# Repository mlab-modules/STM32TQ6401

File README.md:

# STM32TQ6401 - Universal TQFP64 STM32 Microcontroller Module

The STM32TQ6401 is a universal microcontroller module designed for STM32 MCUs in TQFP64 packages. It offers a flexible platform for both development and deployment, with support for a wide range of STM32 devices and power configurations.

## Features

- Compatible with most STM32 MCUs in TQFP64 package (see note in schematics for exceptions)
- Direct battery operation from a CR2032 cell
- USB-C connector for both programming and external power input
- Standard MLAB pin headers for module interconnection to other MLAB modules
- Onboard 32.768 kHz and 16 MHz crystal oscillators for RTC and system clock
- Multiple LDO regulators providing 3.3V from USB or external 5V input
- USB power switch (TPS2051B) for host/device support
- Boot and reset buttons, debug header (SWD), and optional VCAP configuration

## Power Supply

- **Battery Operation:** Directly powered by a CR2032 cell; suitable for ultra-low power STM32 MCUs
- **USB Power:** Supplied through USB-C connector; LDO regulator converts 5V to 3.3V
- **External Power Input:** 2.6 V to 5.2 V via dedicated jumper or header

## Connectivity

- USB-C for firmware upload and serial communication
- SWD (Serial Wire Debug) header for in-circuit debugging
- MLAB standard headers for full I/O access

## Clock Sources

- **Y1:** 32.768 kHz crystal for RTC
- **Y2:** 16 MHz crystal for system clock

### Incompatible STM32 Devices
Some STM32 MCUs are not compatible with this module due to VCAP or other special pin requirements. These include (but are not limited to):

- STM32F030R4Tx, STM32F405RGTx, STM32H7xxRxTx
- STM32G4xxRxTx, STM32L5xxRxTxQ, STM32U5xxRxTxQ

Refer to schematic details for a complete list of incompatible devices.

### Pin Variants

Special attention is required for the following pins due to variant functions:

- VBAT / VLCD
- VCAP / VDDUSB
- BOOT0 / PH3

Refer to MCU datasheets and the module schematic for proper configuration.

## Mounting

- Four 3mm MLAB mounting holes for mechanical stability

## Schematic

For detailed pinout, power configuration, and compatibility, refer to the [STM32TQ6401A schematic](/doc/gen/STM32TQ6401-schematic.pdf).

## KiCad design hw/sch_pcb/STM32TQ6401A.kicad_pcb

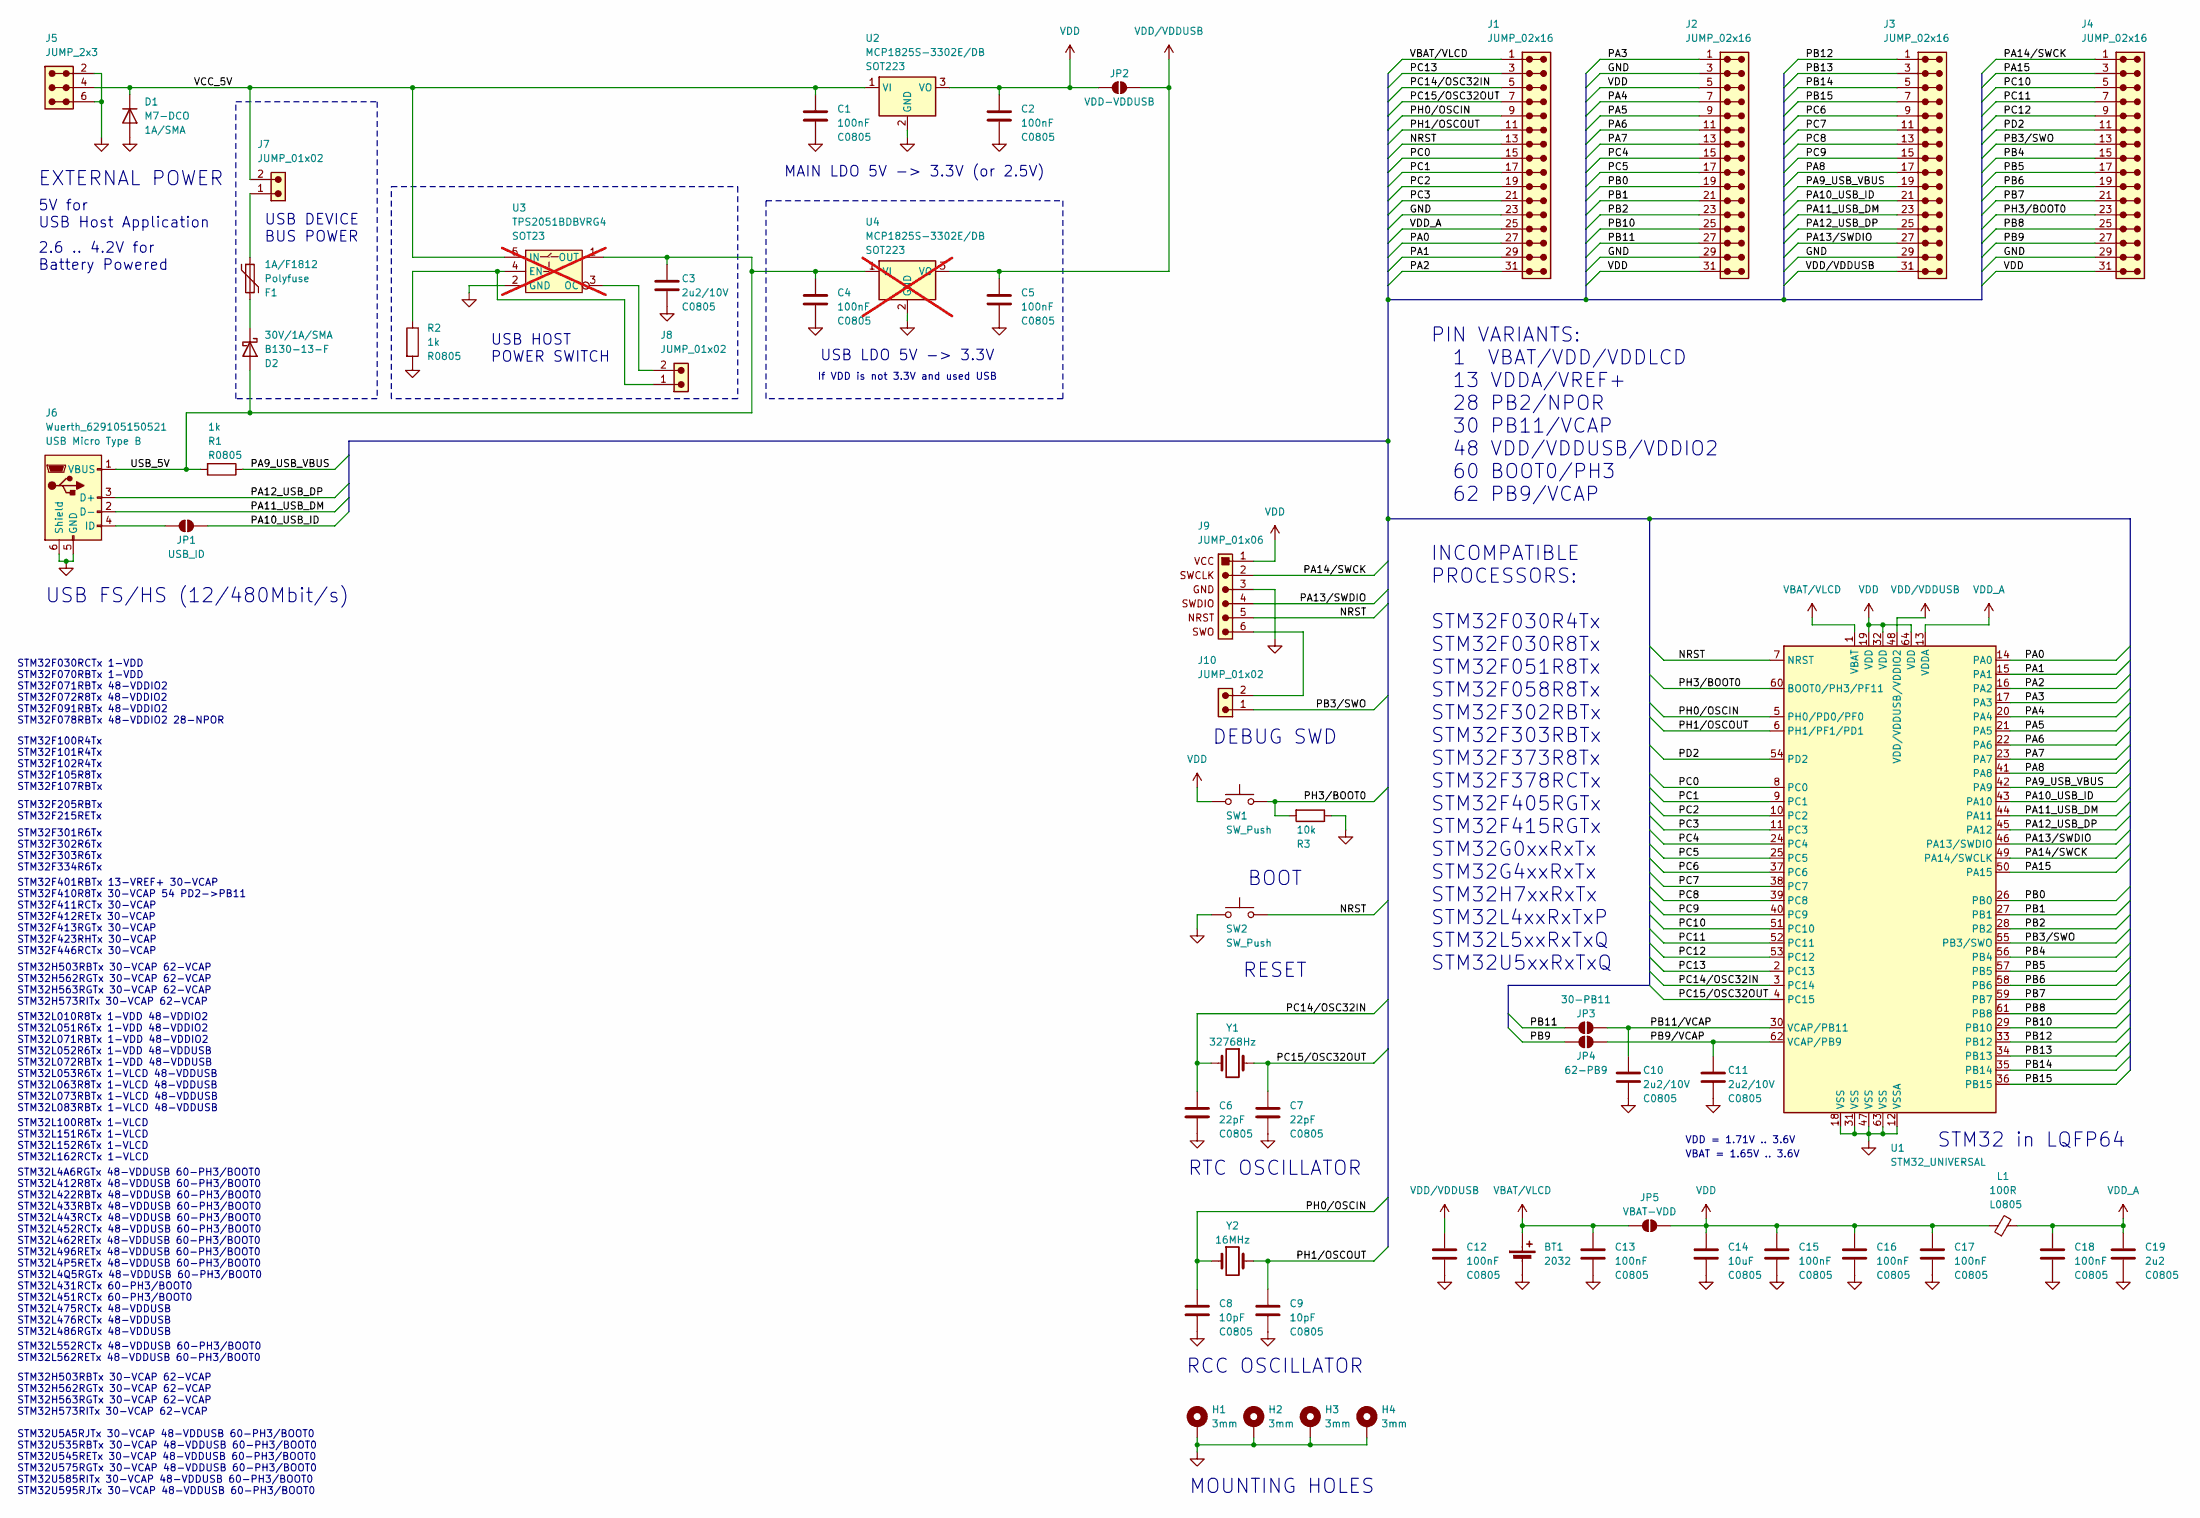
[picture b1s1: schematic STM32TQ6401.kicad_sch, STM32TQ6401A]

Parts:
BT1: 2032; BatteryHolder_Renata_SMTU2032
C1, C2, C4, C5, C12, C13, C15, C16, C17, C18: 100nF; C_0805_2012Metric_Pad1.18x1.45mm_HandSolder
C3, C10, C11: 2u2/10V; C_0805_2012Metric_Pad1.18x1.45mm_HandSolder
C6, C7: 22pF; C_0805_2012Metric_Pad1.18x1.45mm_HandSolder
C8, C9: 10pF; C_0805_2012Metric_Pad1.18x1.45mm_HandSolder
C14: 10uF; C_0805_2012Metric_Pad1.18x1.45mm_HandSolder
C19: 2u2; C_0805_2012Metric_Pad1.18x1.45mm_HandSolder
D1: M7-DCO; D_SMA_Handsoldering
D2: B130-13-F; D_SMA_Handsoldering
F1: Polyfuse; Fuse_1812_4532Metric_Pad1.30x3.40mm_HandSolder
H1, H2, H3, H4: 3mm; MountingHole_3.2mm_M3_DIN965_Pad
J1, J2, J3, J4: JUMP_02x16; PinHeader_2x16_P2.54mm_Vertical
J5: JUMP_2x3; PinHeader_2x03_P2.54mm_Vertical
J6: Wuerth_629105150521; USB_Micro-B_Wuerth_629105150521
J7, J8, J10: JUMP_01x02; PinHeader_1x02_P2.54mm_Vertical
J9: JUMP_01x06; PinHeader_1x06_P2.54mm_Vertical
JP1: USB_ID; SolderJumper-2_P1.3mm_Open_TrianglePad1.0x1.5mm
JP2: VDD-VDDUSB; SolderJumper-2_P1.3mm_Open_TrianglePad1.0x1.5mm
JP3: 30-PB11; SolderJumper-2_P1.3mm_Open_TrianglePad1.0x1.5mm
JP4: 62-PB9; SolderJumper-2_P1.3mm_Open_TrianglePad1.0x1.5mm
JP5: VBAT-VDD; SolderJumper-2_P1.3mm_Open_TrianglePad1.0x1.5mm
L1: 100R; L_0805_2012Metric_Pad1.15x1.40mm_HandSolder
R1, R2: 1k; C_0805_2012Metric_Pad1.18x1.45mm_HandSolder
R3: 10k; C_0805_2012Metric_Pad1.18x1.45mm_HandSolder
SW1, SW2: SW_Push; SW_PUSH_6mm
U1: STM32_UNIVERSAL; LQFP-64_10x10mm_P0.5mm
U2: MCP1825S-3302E/DB; SOT-223-3_TabPin2
U3: TPS2051BDBVRG4; SOT-23-5; not fitted
U4: MCP1825S-3302E/DB; SOT-223-3_TabPin2; not fitted
Y1: 32768Hz; Crystal_AT310_D3.0mm_L10.0mm_Horizontal
Y2: 16MHz; Crystal_HC49-U_Vertical

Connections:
/NRST: J1.13, J1.14, J9.5, SW2.2, U1.7 (NRST)
/PA0: J1.27, J1.28, U1.14 (PA0)
/PA1: J1.29, J1.30, U1.15 (PA1)
/PA2: J1.31, J1.32, U1.16 (PA2)
/PA3: J2.1, J2.2, U1.17 (PA3)
/PA4: J2.7, J2.8, U1.20 (PA4)
/PA5: J2.9, J2.10, U1.21 (PA5)
/PA6: J2.11, J2.12, U1.22 (PA6)
/PA7: J2.13, J2.14, U1.23 (PA7)
/PA8: J3.17, J3.18, U1.41 (PA8)
/PA9_USB_VBUS: J3.19, J3.20, R1.1, U1.42 (PA9)
/PA10_USB_ID: J3.21, J3.22, JP1.2 (B), U1.43 (PA10)
/PA11_USB_DM: J3.23, J3.24, J6.2 (D-), U1.44 (PA11)
/PA12_USB_DP: J3.25, J3.26, J6.3 (D+), U1.45 (PA12)
/PA13/SWDIO: J3.27, J3.28, J9.4, U1.46 (PA13/SWDIO)
/PA14/SWCK: J4.1, J4.2, J9.2, U1.49 (PA14/SWCLK)
/PA15: J4.3, J4.4, U1.50 (PA15)
/PB0: J2.19, J2.20, U1.26 (PB0)
/PB1: J2.21, J2.22, U1.27 (PB1)
/PB2: J2.23, J2.24, U1.28 (PB2)
/PB3/SWO: J4.13, J4.14, J10.1, U1.55 (PB3/SWO)
/PB4: J4.15, J4.16, U1.56 (PB4)
/PB5: J4.17, J4.18, U1.57 (PB5)
/PB6: J4.19, J4.20, U1.58 (PB6)
/PB7: J4.21, J4.22, U1.59 (PB7)
/PB8: J4.25, J4.26, U1.61 (PB8)
/PB9: J4.27, J4.28, JP4.1 (A)
/PB9/VCAP: C11.1, JP4.2 (B), U1.62 (VCAP/PB9)
/PB10: J2.25, J2.26, U1.29 (PB10)
/PB11: J2.27, J2.28, JP3.1 (A)
/PB11/VCAP: C10.1, JP3.2 (B), U1.30 (VCAP/PB11)
/PB12: J3.1, J3.2, U1.33 (PB12)
/PB13: J3.3, J3.4, U1.34 (PB13)
/PB14: J3.5, J3.6, U1.35 (PB14)
/PB15: J3.7, J3.8, U1.36 (PB15)
/PC0: J1.15, J1.16, U1.8 (PC0)
/PC1: J1.17, J1.18, U1.9 (PC1)
/PC2: J1.19, J1.20, U1.10 (PC2)
/PC3: J1.21, J1.22, U1.11 (PC3)
/PC4: J2.15, J2.16, U1.24 (PC4)
/PC5: J2.17, J2.18, U1.25 (PC5)
/PC6: J3.9, J3.10, U1.37 (PC6)
/PC7: J3.11, J3.12, U1.38 (PC7)
/PC8: J3.13, J3.14, U1.39 (PC8)
/PC9: J3.15, J3.16, U1.40 (PC9)
/PC10: J4.5, J4.6, U1.51 (PC10)
/PC11: J4.7, J4.8, U1.52 (PC11)
/PC12: J4.9, J4.10, U1.53 (PC12)
/PC13: J1.3, J1.4, U1.2 (PC13)
/PC14/OSC32IN: C6.1, J1.5, J1.6, U1.3 (PC14), Y1.2
/PC15/OSC32OUT: C7.1, J1.7, J1.8, U1.4 (PC15), Y1.1
/PD2: J4.11, J4.12, U1.54 (PD2)
/PH0/OSCIN: C8.1, J1.9, J1.10, U1.5 (PH0/PD0/PF0), Y2.1
/PH1/OSCOUT: C9.1, J1.11, J1.12, U1.6 (PH1/PF1/PD1), Y2.2
/PH3/BOOT0: J4.23, J4.24, R3.2, SW1.2, U1.60 (BOOT0/PH3/PF11)
/USB_5V: C3.1, C4.1, D2.2 (A), J6.1 (VBUS), R1.2, U3.1 (OUT), U4.1 (VI)
/VCC_5V: C1.1, D1.1 (K), J5.3, J5.4, J7.2, U2.1 (VI), U3.5 (IN)
GND: BT1.2 (-), C1.2, C2.2, C3.2, C4.2, C5.2, C6.2, C7.2, C8.2, C9.2, C10.2, C11.2, C12.2, C13.2, C14.2, C15.2, C16.2, C17.2, C18.2, C19.2, D1.2 (A), H1.1, H2.1, H3.1, H4.1, J1.23, J1.24, J2.3, J2.4, J2.29, J2.30, J3.29, J3.30, J4.29, J4.30, J5.1, J5.2, J5.5, J5.6, J6.5 (GND), J6.6 (Shield), J9.3, R2.2, R3.1, SW2.1, U1.12 (VSSA), U1.18 (VSS), U1.31 (VSS), U1.47 (VSS), U1.63 (VSS), U2.2 (GND), U3.2 (GND), U4.2 (GND)
unnamed: D2.1 (K), F1.2
unnamed: J6.4 (ID), JP1.1 (A)
unnamed: F1.1, J7.1
unnamed: J8.1, R2.1, U3.4 (EN)
unnamed: J8.2, U3.3 (OC)
unnamed: J9.6, J10.2
VDD: C2.1, C14.1, C15.1, C16.1, C17.1, J2.5, J2.6, J2.31, J2.32, J4.31, J4.32, J9.1, JP2.1 (A), JP5.2 (B), L1.1, SW1.1, U1.19 (VDD), U1.32 (VDD), U1.64 (VDD), U2.3 (VO)
VDD_A: C18.1, C19.1, J1.25, J1.26, L1.2, U1.13 (VDDA)

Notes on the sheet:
USB HOST POWER SWITCH
VDD = 1.71V .. 3.6V
STM32F401RBTx 13-VREF+ 30-VCAP STM32F410R8Tx 30-VCAP 54 PD2->PB11 STM32F411RCTx 30-VCAP STM32F412RETx 30-VCAP STM32F413RGTx 30-VCAP STM32F423RHTx 30-VCAP STM32F446RCTx 30-VCAP
STM32F301R6Tx STM32F302R6Tx STM32F303R6Tx STM32F334R6Tx
If VDD is not 3.3V and used USB
2.6 .. 4.2V for Battery Powered
STM32F100R4Tx STM32F101R4Tx STM32F102R4Tx STM32F105R8Tx STM32F107RBTx
STM32F205RBTx STM32F215RETx
RCC OSCILLATOR
USB DEVICE BUS POWER
STM32L010R8Tx 1-VDD 48-VDDIO2 STM32L051R6Tx 1-VDD 48-VDDIO2 STM32L071RBTx 1-VDD 48-VDDIO2 STM32L052R6Tx 1-VDD 48-VDDUSB STM32L072RBTx 1-VDD 48-VDDUSB STM32L053R6Tx 1-VLCD 48-VDDUSB STM32L063R8Tx 1-VLCD 48-VDDUSB STM32L073RBTx 1-VLCD 48-VDDUSB STM32L083RBTx 1-VLCD 48-VDDUSB
MAIN LDO 5V -> 3.3V (or 2.5V)
DEBUG SWD
MOUNTING HOLES
USB FS/HS (12/480Mbit/s)
USB LDO 5V -> 3.3V
5V for USB Host Application
STM32L4A6RGTx 48-VDDUSB 60-PH3/BOOT0 STM32L412R8Tx 48-VDDUSB 60-PH3/BOOT0 STM32L422RBTx 48-VDDUSB 60-PH3/BOOT0 STM32L433RBTx 48-VDDUSB 60-PH3/BOOT0 STM32L443RCTx 48-VDDUSB 60-PH3/BOOT0 STM32L452RCTx 48-VDDUSB 60-PH3/BOOT0 STM32L462RETx 48-VDDUSB 60-PH3/BOOT0 STM32L496RETx 48-VDDUSB 60-PH3/BOOT0 STM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
STM32U5A5RJTx 30-VCAP 48-VDDUSB 60-PH3/BOOT0 STM32U535RBTx 30-VCAP 48-VDDUSB 60-PH3/BOOT0 STM32U545RETx 30-VCAP 48-VDDUSB 60-PH3/BOOT0 STM32U575RGTx 30-VCAP 48-VDDUSB 60-PH3/BOOT0 STM32U585RITx 30-VCAP 48-VDDUSB 60-PH3/BOOT0 STM32U595RJTx 30-VCAP 48-VDDUSB 60-PH3/BOOT0
STM32L552RCTx 48-VDDUSB 60-PH3/BOOT0 STM32L562RETx 48-VDDUSB 60-PH3/BOOT0
PIN VARIANTS: 1 VBAT/VDD/VDDLCD 13 VDDA/VREF+ 28 PB2/NPOR 30 PB11/VCAP 48 VDD/VDDUSB/VDDIO2 60 BOOT0/PH3 62 PB9/VCAP
RESET
RTC OSCILLATOR
STM32F030RCTx 1-VDD STM32F070RBTx 1-VDD STM32F071RBTx 48-VDDIO2 STM32F072R8Tx 48-VDDIO2 STM32F091RBTx 48-VDDIO2 STM32F078RBTx 48-VDDIO2 28-NPOR
STM32H503RBTx 30-VCAP 62-VCAP STM32H562RGTx 30-VCAP 62-VCAP STM32H563RGTx 30-VCAP 62-VCAP STM32H573RITx 30-VCAP 62-VCAP
STM32 in LQFP64
BOOT
EXTERNAL POWER
INCOMPATIBLE PROCESSORS: STM32F030R4Tx STM32F030R8Tx STM32F051R8Tx STM32F058R8Tx STM32F302RBTx STM32F303RBTx STM32F373R8Tx STM32F378RCTx STM32F405RGTx STM32F415RGTx STM32G0xxRxTx STM32G4xxRxTx STM32H7xxRxTx STM32L4xxRxTxP STM32L5xxRxTxQ STM32U5xxRxTxQ
STM32L100R8Tx 1-VLCD STM32L151R6Tx 1-VLCD STM32L152R6Tx 1-VLCD STM32L162RCTx 1-VLCD
VBAT = 1.65V .. 3.6V

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
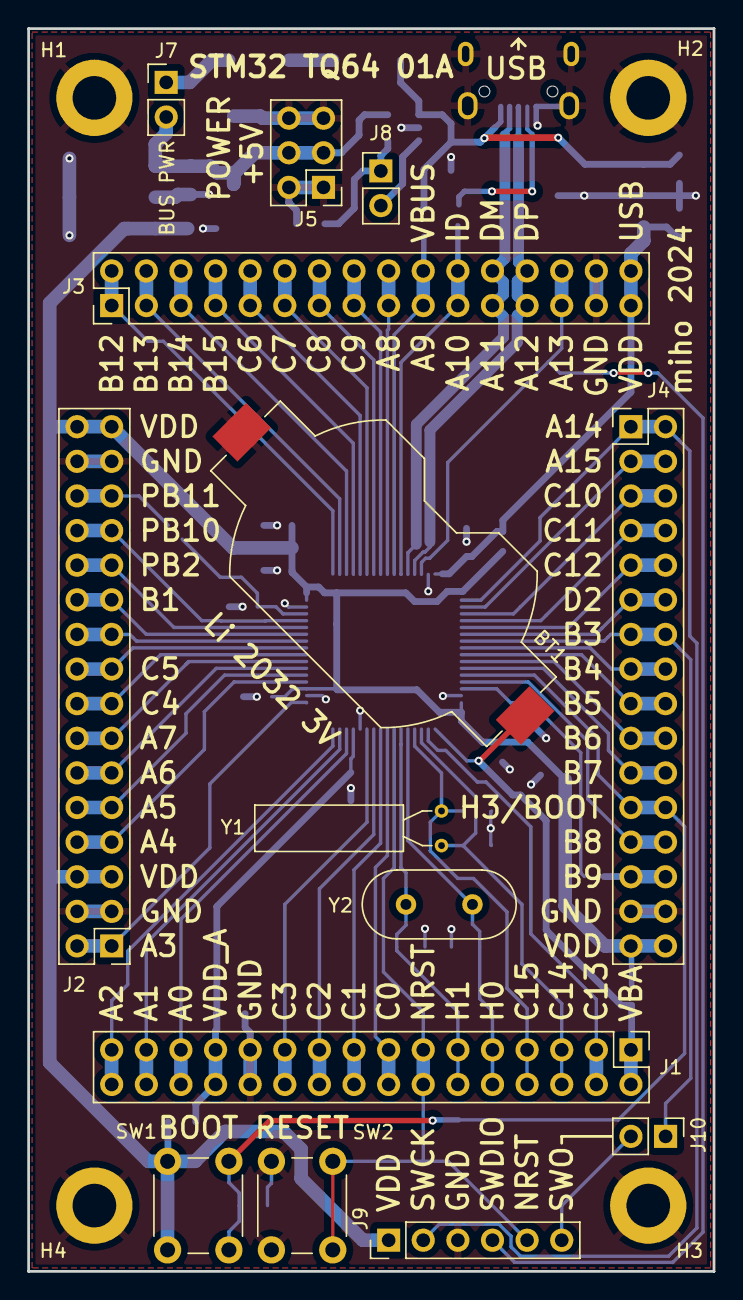
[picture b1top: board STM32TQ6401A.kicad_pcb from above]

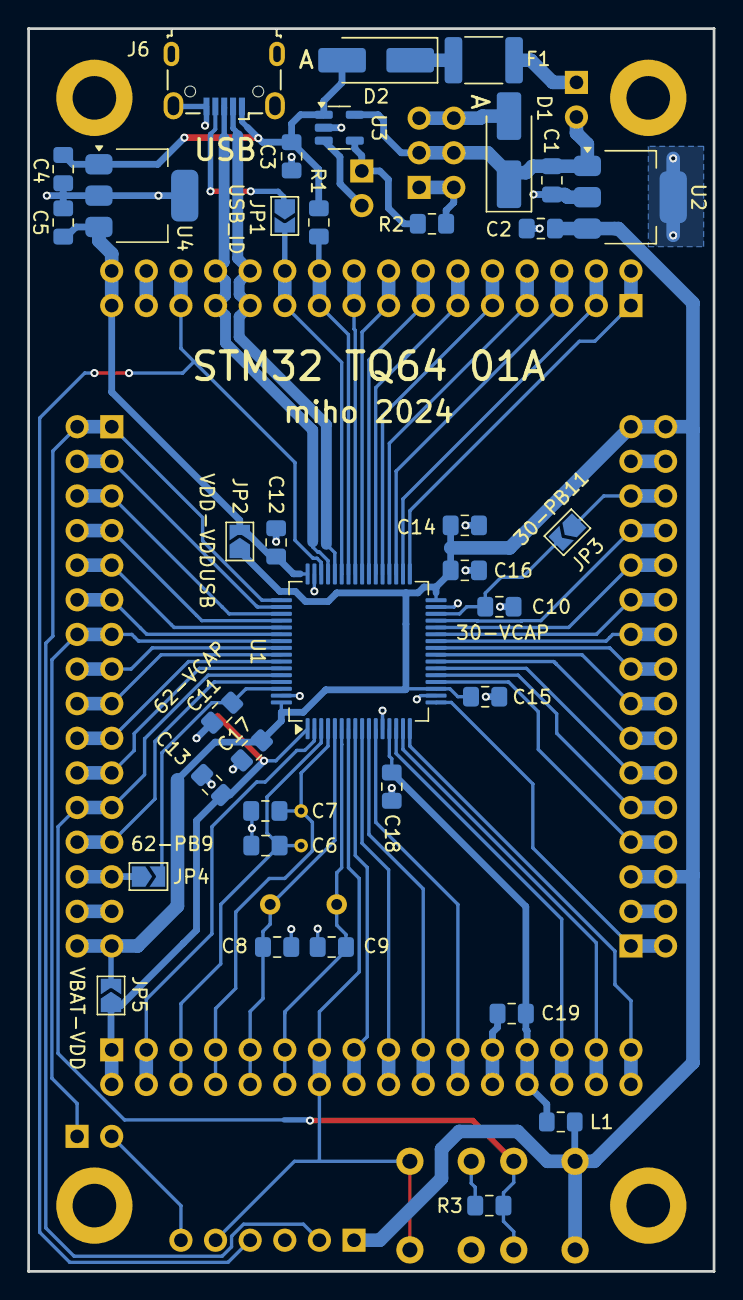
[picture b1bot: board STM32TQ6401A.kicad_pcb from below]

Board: 2 copper layers, 50.3 x 91.2 mm, 54 parts (36 on the bottom side), 68 nets.

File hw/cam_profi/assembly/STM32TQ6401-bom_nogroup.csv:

Component,Description,Part,References,Value,Footprint,Quantity Per PCB,Datasheet,sim.device,sim.pins
1,Single-cell battery,Battery_Cell,BT1,2032,BatteryHolder_Renata_SMTU2032,1,https://cz.mouser.com/datasheet/2/346/renata_smtu2032-lf-120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,,
2,C0805,C,C8C9,10pF,C_0805_2012Metric_Pad1.18x1.45mm_HandSolder,2,~,,
3,C0805,C,C6C7,22pF,C_0805_2012Metric_Pad1.18x1.45mm_HandSolder,2,~,,
4,C0805,C,C1C2C4C5C12C13C15C16C17C18,100nF,C_0805_2012Metric_Pad1.18x1.45mm_HandSolder,10,~,,
5,C0805,C,C19,2u2,C_0805_2012Metric_Pad1.18x1.45mm_HandSolder,1,~,,
6,C0805,C,C14,10uF,C_0805_2012Metric_Pad1.18x1.45mm_HandSolder,1,~,,
7,C0805,C,C3C10C11,2u2/10V,C_0805_2012Metric_Pad1.18x1.45mm_HandSolder,3,~,,
8,30V/1A/SMA,D_Schottky,D2,B130-13-F,D_SMA_Handsoldering,1,~,,
9,1A/SMA,D,D1,M7-DCO,D_SMA_Handsoldering,1,~,D,1=K 2=A
10,1A/F1812,Polyfuse,F1,Polyfuse,Fuse_1812_4532Metric_Pad1.30x3.40mm_HandSolder,1,~,,
11,"Header connector, single row, 01x02, script generated",JUMP_01x02_M,J7J8J10,JUMP_01x02,PinHeader_1x02_P2.54mm_Vertical,3,~,,
12,"Header connector, single row, 01x06, script generated",STM32_SWD_JUMP6,J9,JUMP_01x06,PinHeader_1x06_P2.54mm_Vertical,1,~,,
13,"Header connector, double row, 02x16,, script generated",JUMP_02x16_M_connected_L,J1J2J3J4,JUMP_02x16,PinHeader_2x16_P2.54mm_Vertical,4,~,,
14,"Header connector, double row, 02x03,, script generated",JUMP_02x03_M_connected_R,J5,JUMP_2x3,PinHeader_2x03_P2.54mm_Vertical,1,~,,
15,USB Micro Type B,USB_B_Micro,J6,Wuerth_629105150521,USB_Micro-B_Wuerth_629105150521,1,~,,
16,L0805,FerriteBead_Small,L1,100R,L_0805_2012Metric_Pad1.15x1.40mm_HandSolder,1,~,,
17,R0805,R,R1R2,1k,C_0805_2012Metric_Pad1.18x1.45mm_HandSolder,2,~,,
18,Resistor,R,R3,10k,C_0805_2012Metric_Pad1.18x1.45mm_HandSolder,1,~,,
19,"Push button switch, generic, two pins",SW_Push,SW1SW2,SW_Push,SW_PUSH_6mm,2,~,,
20,SOT223,MCP1825S,U2,MCP1825S-3302E/DB,SOT-223-3_TabPin2,1,http://ww1.microchip.com/downloads/en/devicedoc/22056b.pdf,,
21,"STMicroelectronics Arm Cortex-M33 MCU, 128KB flash, 32KB RAM, 250 MHz, 49 GPIO, LQFP64",STM32H503RBTx,U1,STM32_UNIVERSAL,LQFP-64_10x10mm_P0.5mm,1,https://www.st.com/resource/en/datasheet/stm32h503rb.pdf,,
22,Two pin crystal,Crystal,Y2,16MHz,Crystal_HC49-U_Vertical,1,~,,
23,Two pin crystal,Crystal,Y1,32768Hz,Crystal_AT310_D3.0mm_L10.0mm_Horizontal,1,~,,

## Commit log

2025-03-22 Update workflow files
2025-03-22 Update metadata files
2025-03-22 Initial project from MIHO.
2025-05-06 Update project description and metatadata.
2025-05-06 Renaming project to get automatic action working.
2025-05-06 Update actions products
2025-05-06 Add images to readme.
2025-05-06 Update README.md
    Fix image paths.
